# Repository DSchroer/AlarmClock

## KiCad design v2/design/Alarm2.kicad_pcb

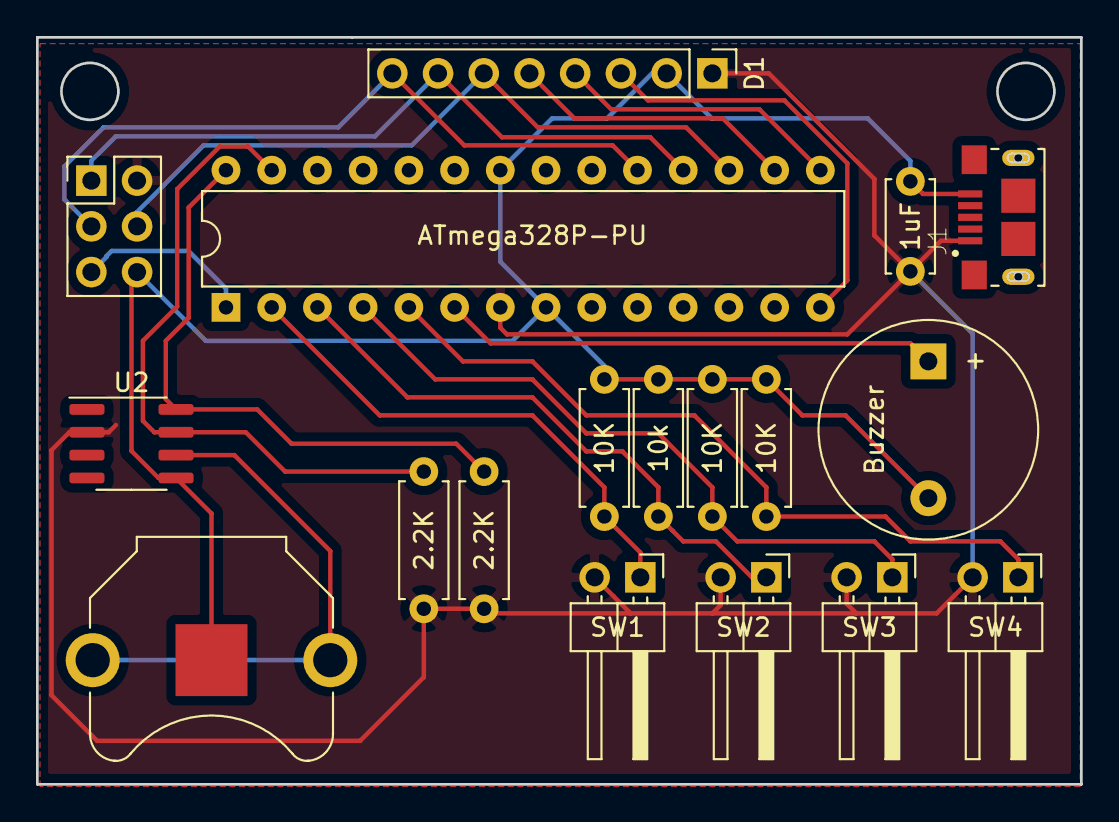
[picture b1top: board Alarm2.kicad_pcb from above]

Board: 2 copper layers, 58.0 x 41.5 mm, 18 parts (0 on the bottom side), 15 nets.

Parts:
BT1: Battery_Cell; BatteryHolder_Keystone_3001_1x12mm
BZ1: Buzzer; Buzzer_12x9.5RM7.6
C1: 1uF; C_Disc_D5.0mm_W2.5mm_P5.00mm
D1: Nokia-5110; PinHeader_1x08_P2.54mm_Vertical
J1: 10118193-0001LF; FCI_10118193-0001LF
J2: AVR-ISP-6; PinHeader_2x03_P2.54mm_Vertical
R1, R3, R4: 10K; R_Axial_DIN0207_L6.3mm_D2.5mm_P7.62mm_Horizontal
R2: 10k; R_Axial_DIN0207_L6.3mm_D2.5mm_P7.62mm_Horizontal
R5, R6: 2.2K; R_Axial_DIN0207_L6.3mm_D2.5mm_P7.62mm_Horizontal
SW1, SW2, SW3, SW4: SW_Push; PinHeader_1x02_P2.54mm_Horizontal
U1: ATmega328P-PU; DIP-28_W7.62mm
U2: DS3231MZ; SOIC-8_3.9x4.9mm_P1.27mm

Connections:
unnamed: BT1.1, U2.6
unnamed: BT1.2, BZ1.2, C1.2, D1.2, J1.5, J2.6, R1.1, R2.1, R3.1, R4.1, U1.8, U1.22, U2.5
unnamed: BZ1.1, U1.6
unnamed: C1.1, D1.1, J1.1, J2.2, R5.1, R6.1, SW1.2, SW2.2, SW3.2, SW4.2, U1.7, U2.2
unnamed: J1.S1, J1.S2, J1.S3, J1.S4, J1.S5, J1.S6
unnamed: J2.1, U1.18
unnamed: J2.3, U1.19
unnamed: J2.4, U1.17
unnamed: J2.5, U1.1
unnamed: R1.2, SW1.1, U1.2
unnamed: R2.2, SW2.1, U1.3
unnamed: R3.2, SW3.1, U1.4
unnamed: R4.2, SW4.1, U1.5
unnamed: R5.2, U1.27, U2.7
unnamed: R6.2, U1.28, U2.8

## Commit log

2018-02-25 Initial Software
2018-02-25 Initial Time Setup
2018-03-06 Added alarms
2018-03-25 Added light controls
2018-12-15 Updated Gitignore
2018-12-15 removed scons file
2018-12-15 Added properties update
2019-04-08 Moving old files to v1
2019-04-08 Added new version files
2019-04-09 refactoring to a local c++ model
2019-05-11 working on rebuilding a modular code base
2019-05-12 Setup local rendering
2019-05-12 added comments
2019-05-12 Moving to libsfml
2019-05-13 Added the base menu system
2019-07-01 Added local clock support
2019-07-01 Renamed main menu
2019-07-01 Added buttons support
2019-07-01 Added main menu
2019-07-01 Started Time Editor
2019-07-01 Finished time editing
2019-07-03 Started working on the alarm subsystem
2019-07-03 Started working on heap template
2019-07-20 Completed heap implementation
2019-07-20 Fixed build debugging
2019-08-01 Moved to using CMake
2019-08-01 Solidifying alarm system
2019-08-01 Added Snoozing
2019-08-05 Added alarm system + alarm view
2019-09-07 Added alarm list view
2019-09-07 Started alarm edit screen
2019-09-08 Added the beginning of the Alarm Edit Menu. Fixed deployment builds.
2019-09-08 Fixing gitignore
2019-09-08 Added backlight support
2019-09-08 Completed alarm edit screen Fixed alarm screen
2019-09-08 Added alarm storage Added buzzer to alarm screen Added light to alarm screen
2019-09-08 Cleaning up alarm menu
2019-11-17 Fixing gitignore for local files
2019-11-17 Fixing unit tests
2019-11-17 Added inline vector constructor
2019-11-17 Added base call
2019-11-17 Working on generic list menu
2019-11-30 Added case files
2020-03-20 Fixing memory issues with Vector
2020-04-11 Firmware version 1.0
2020-05-17 Added V2 PCB
2020-08-29 Fixing snoozed alarm bug
2020-08-29 Added wait to enter menu on home screen
2020-10-12 Updated RTC reading
